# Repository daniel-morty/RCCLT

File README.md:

# ESPNOW Basic Example

This is a very basic example to get up and running with ESP-NOW using ESP-IDF. While the included example in the IDF is comprehensive and secure, this example should allow for faster understanding and testing.

The slave will simply send a random value and the state of GPIO 0 (typically attached to a button named '0', 'BOOT' or 'PROG' on most dev boards) to the broadcast address. The master will receive and log it.

To customise the payload, simply change the struct in espnow_basic_config.h, and edit my_slave.c and my_master.c to populate and parse respectively.

See espnow_basic_config.h for more.

============================================================
mac of remote/car pair 1
remote	f4:12:fa:1b:3e:b0
car:	f4:12:fa:1b:84:88

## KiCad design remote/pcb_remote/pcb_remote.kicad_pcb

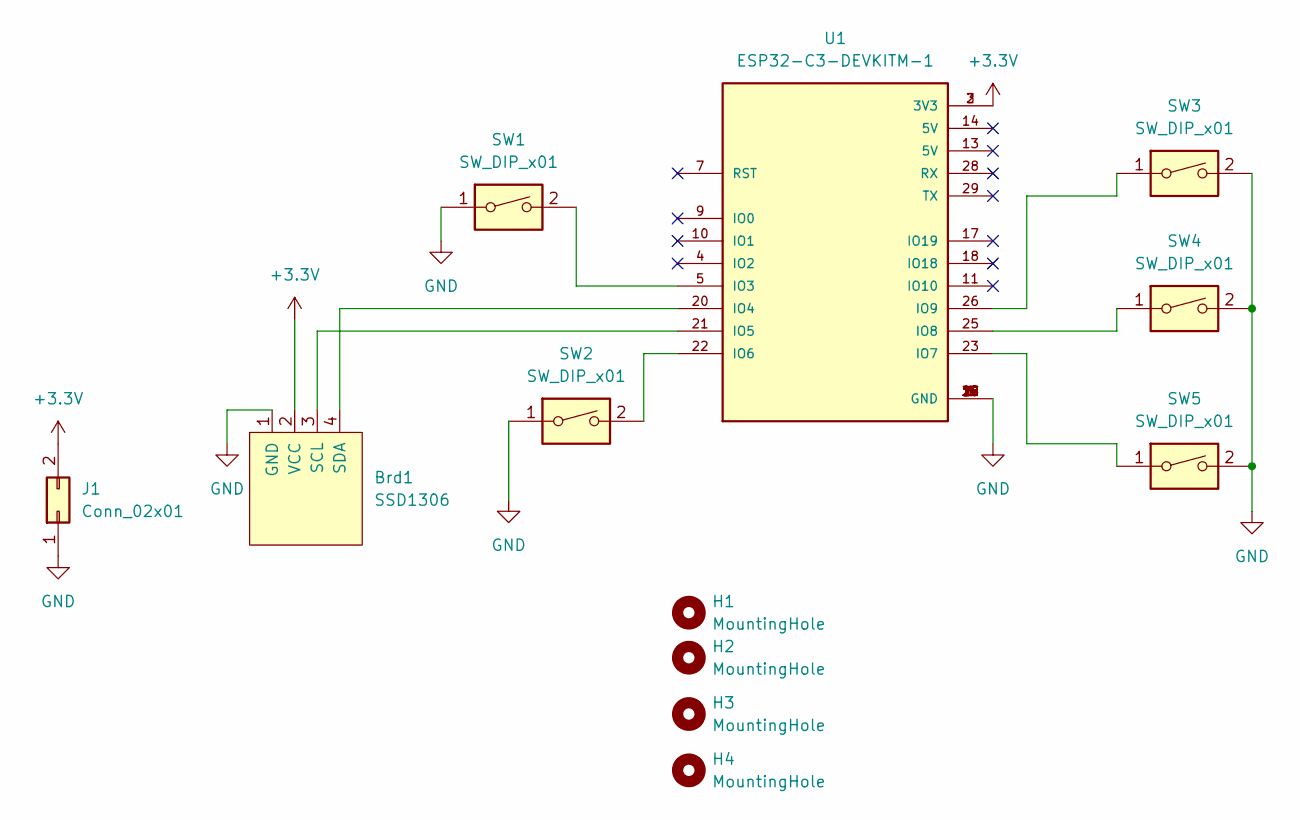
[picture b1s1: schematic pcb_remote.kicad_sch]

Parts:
Brd1: SSD1306; 128x64OLED
H1, H2, H3, H4: MountingHole; MountingHole_2.2mm_M2
J1: Conn_02x01; PinHeader_1x02_P2.54mm_Vertical
SW1, SW2, SW3, SW4, SW5: SW_DIP_x01; SW_PUSH-12mm
U1: ESP32-C3-DEVKITM-1; XCVR_ESP32-C3-DEVKITM-1

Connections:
+3V3: Brd1.2 (VCC), J1.2, U1.2 (3V3), U1.3 (3V3)
GND: Brd1.1 (GND), J1.1, SW1.1, SW2.1, SW3.2, SW4.2, SW5.2, U1.1 (GND), U1.6 (GND), U1.8 (GND), U1.12 (GND), U1.15 (GND), U1.16 (GND), U1.19 (GND), U1.24 (GND), U1.27 (GND), U1.30 (GND)
unnamed: Brd1.3 (SCL), U1.21 (IO5)
unnamed: Brd1.4 (SDA), U1.20 (IO4)
unnamed: SW1.2, U1.5 (IO3)
unnamed: SW2.2, U1.22 (IO6)
unnamed: SW3.1, U1.26 (IO9)
unnamed: SW4.1, U1.25 (IO8)
unnamed: SW5.1, U1.23 (IO7)

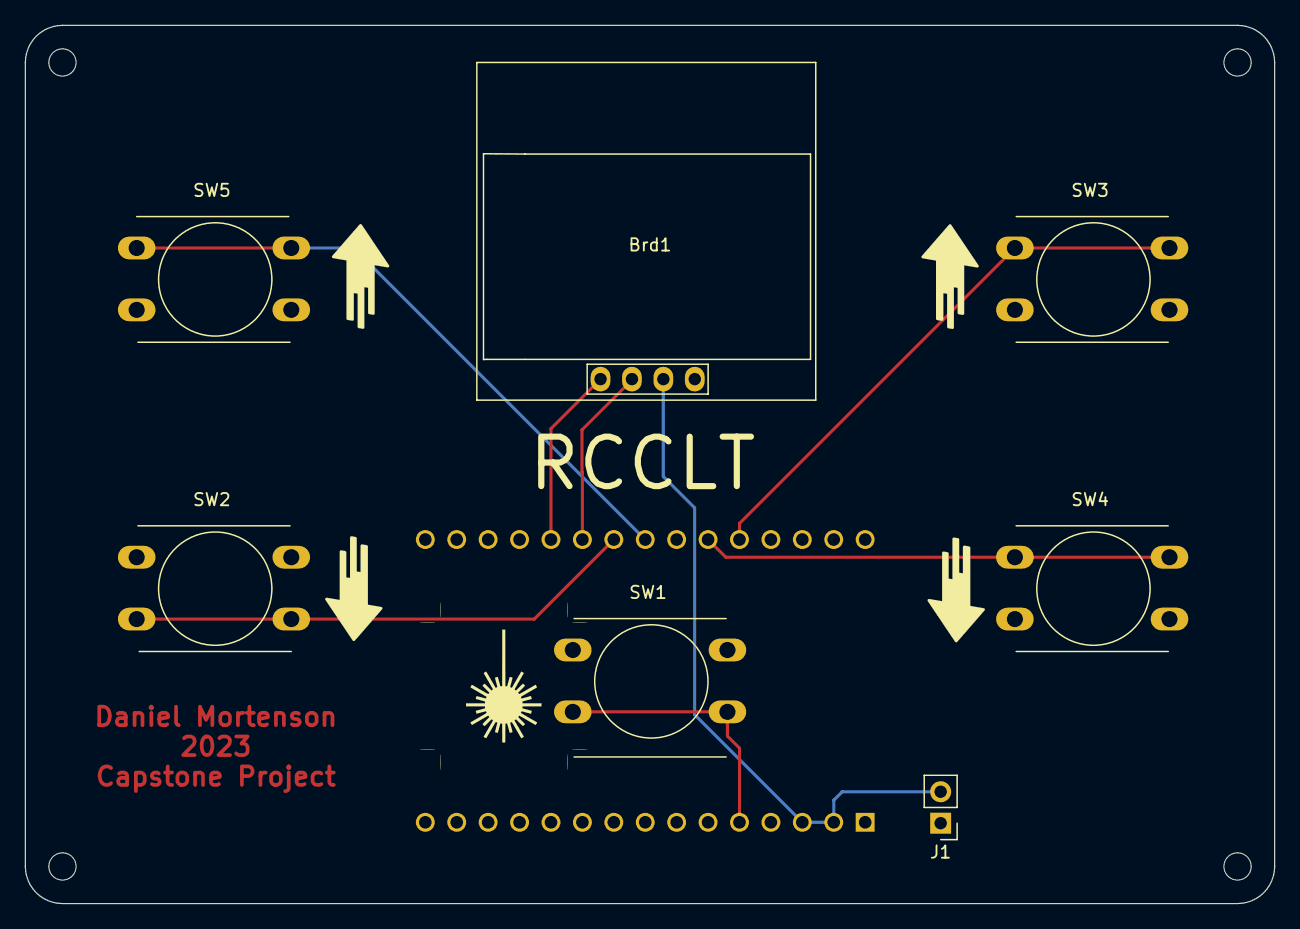
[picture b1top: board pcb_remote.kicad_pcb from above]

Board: 2 copper layers, 101.0 x 71.0 mm, 12 parts (1 on the bottom side), 9 nets.

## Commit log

2023-01-19 trim rtos, buttons control motor
2023-01-19 remove unnecessary files
2023-01-20 add todo
2023-01-20 add laser shoot capability
2023-01-31 add more mac addresses, and easy way to switch car/remote pair
2023-01-31 car shoots laser, need to call get hit function
2023-02-08 add scoreboard, change project names in CMakeLists.txt files
2023-02-09 basic scoreboard function complete, still long way to go though
2023-03-02 add screen to remote, add message from base to remote
2023-03-08 seperated files
2023-03-08 car sending hit_report
2023-03-08 fix automatic sending of score_update
2023-03-24 add interrupts to remote
2023-03-27 remove redundant line from remote main.c
2023-03-29 different approuch to it_init
2023-03-30 add delay to main loop
2023-03-30 add flavortext.h, not yet used
2023-03-30 fix laser, add boot text
2023-04-14 add webserver and webpage to base station
2023-04-14 add mac addresses for all cars for easy compiling
2023-04-18 add pcb files
2023-04-18 fix espnow
2023-04-26 update git ignore
2023-04-28 change laser protocol, other error fixes
2023-05-02 add kill signal to car, may remove later
2023-05-03 right before senior design night
2023-07-07 commit deleted swap files
